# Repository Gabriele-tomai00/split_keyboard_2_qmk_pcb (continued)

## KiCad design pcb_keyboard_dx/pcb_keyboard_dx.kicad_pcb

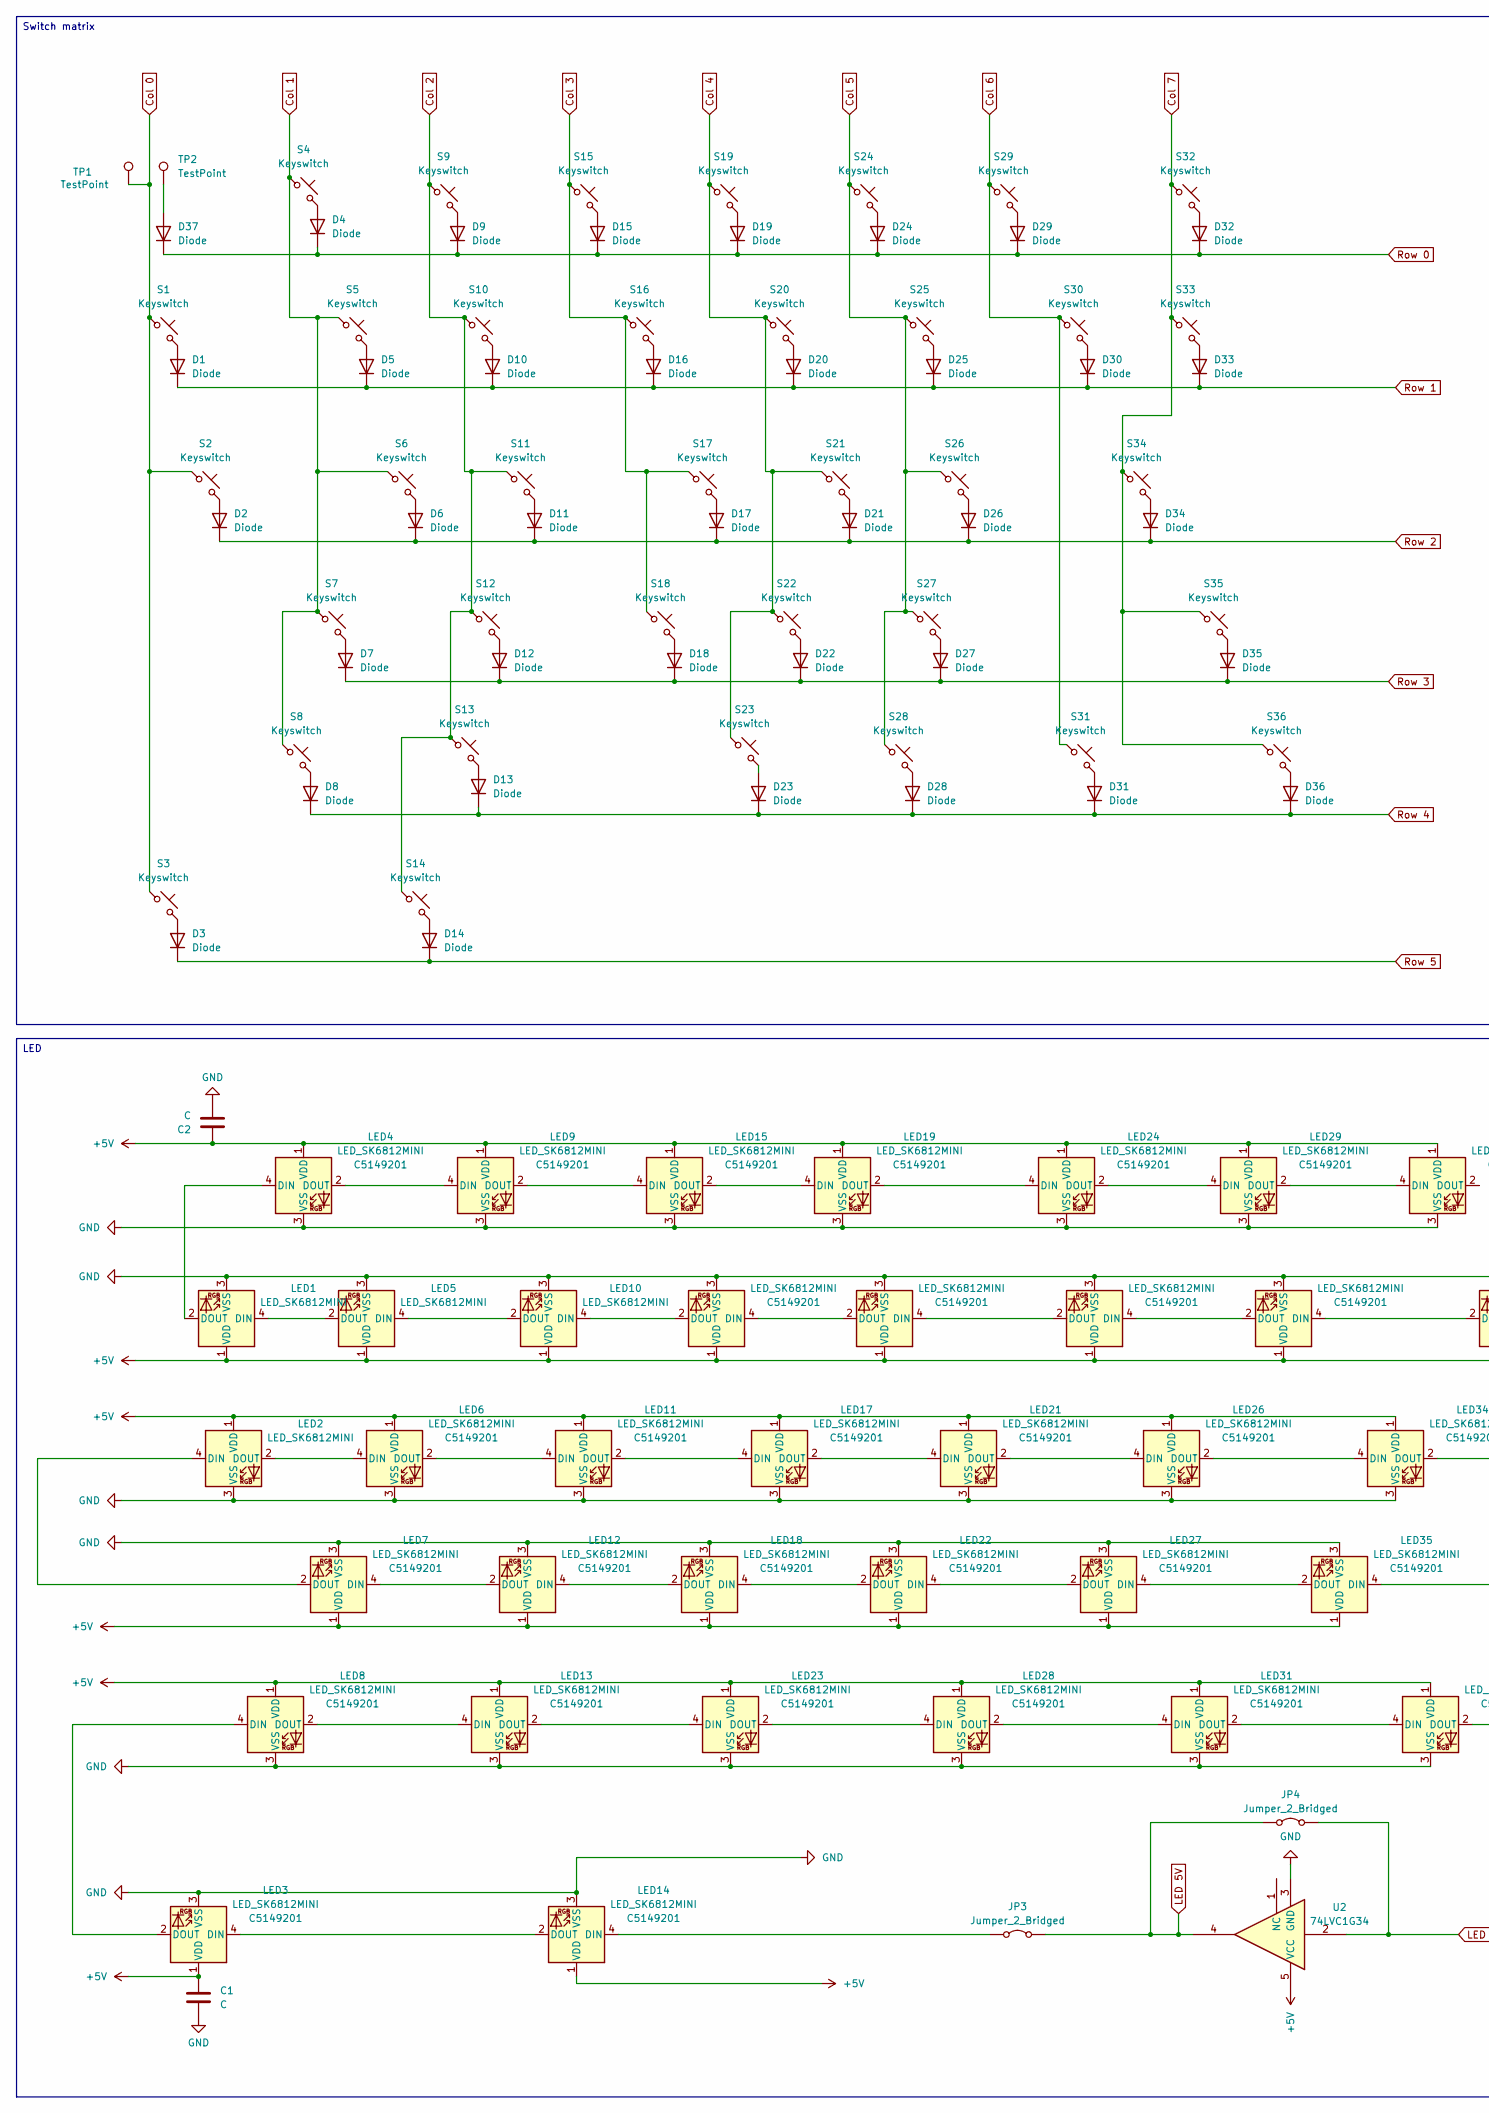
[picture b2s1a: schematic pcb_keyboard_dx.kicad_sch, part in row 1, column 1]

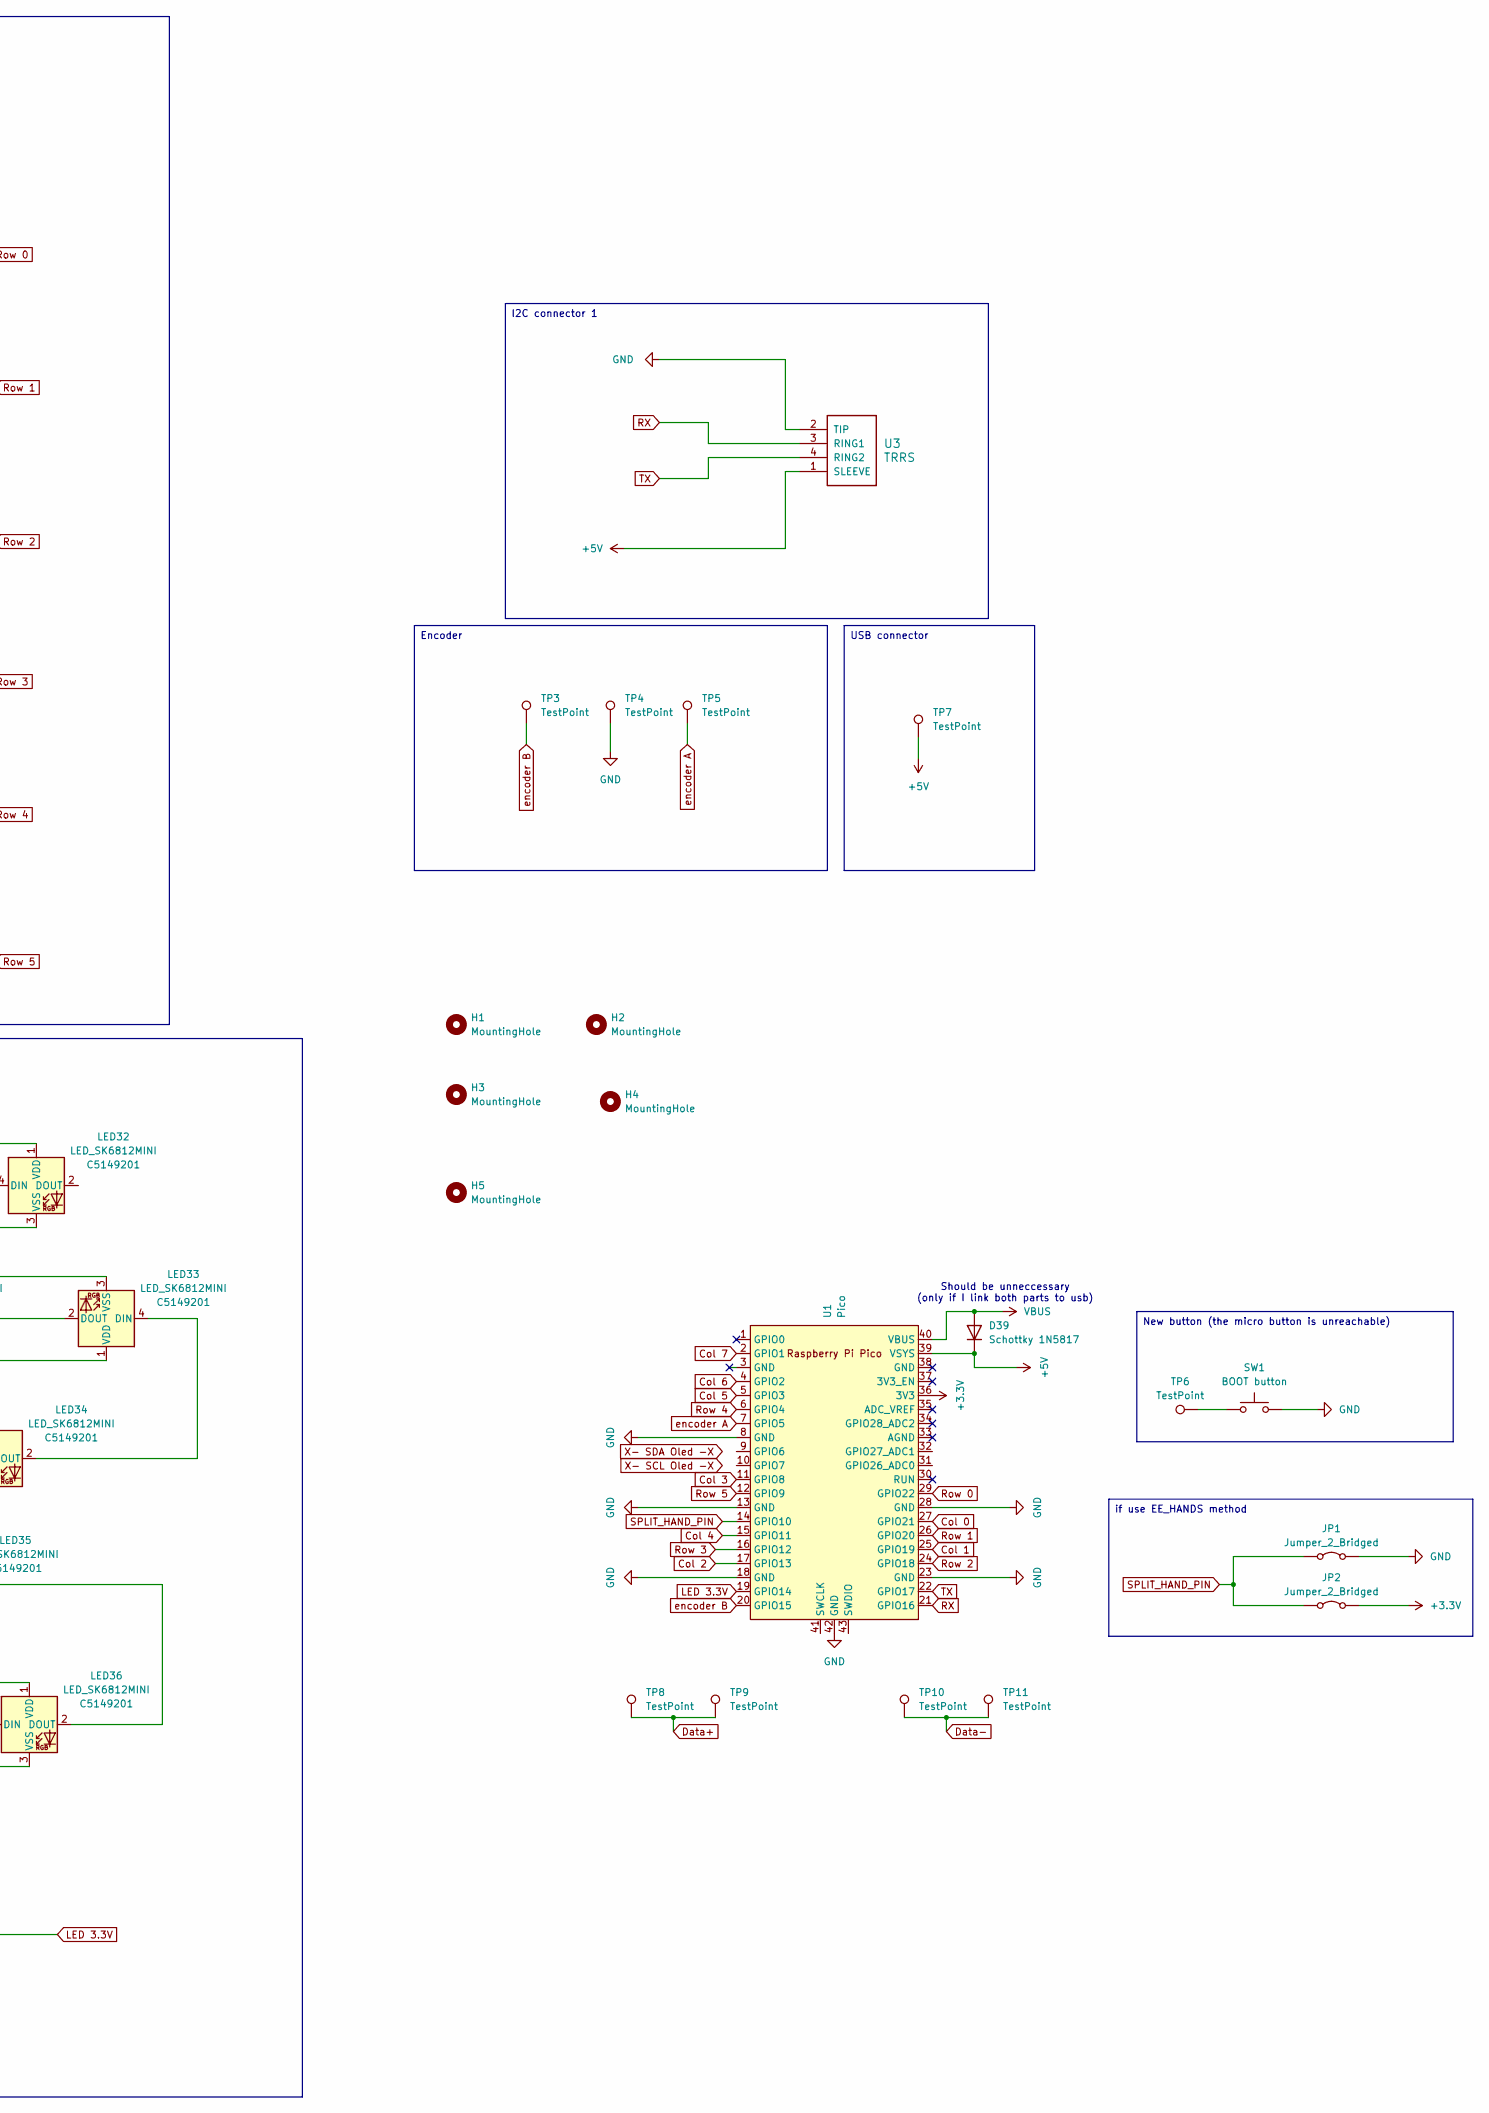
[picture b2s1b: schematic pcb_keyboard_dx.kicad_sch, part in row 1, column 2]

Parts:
C1, C2: C; C_1812_4532Metric_Pad1.57x3.40mm_HandSolder
D1, D2, D3, D4, D5, D6, D7, D8, D9, D10, D11, D12, D13, D14, D15, D16, D17, D18, D19, D20, D21, D22, D23, D24, D25, D26, D27, D28, D29, D30, D31, D32, D33, D34, D35, D36, D37: Diode; D_SOD-123_DO-35_Hybrid_DoubleSided_V2
D39: Schottky 1N5817; D_SOD-123_DO-35_Hybrid_DoubleSided_V2
H1, H2, H3, H4: MountingHole; MountingHole_2.2mm_M2
H5: MountingHole; MountingHole_3.2mm_M3
JP1, JP2, JP3, JP4: Jumper_2_Bridged; SolderJumper-2_P1.3mm_Bridged2Bar_Pad1.0x1.5mm
LED1, LED2, LED3, LED4, LED5, LED6, LED7, LED8, LED9, LED10, LED11, LED12, LED13, LED14, LED15, LED16, LED17, LED18, LED19, LED20, LED21, LED22, LED23, LED24, LED25, LED26, LED27, LED28, LED29, LED30, LED31, LED32, LED33, LED34, LED35, LED36: LED_SK6812MINI; LCSC C5149201
S1, S2, S4, S5, S6, S7, S9, S10, S11, S12, S15, S16, S17, S18, S19, S20, S21, S22, S24, S25, S26, S27, S29, S30: Keyswitch; Hotswap_MX_1.00u
S3: Keyswitch; Choc_V1_1.00u
S8: Keyswitch; Hotswap_MX_1.75u
S13, S33: Keyswitch; Hotswap_MX_1.50u
S14: Keyswitch; Choc_V1_1.75u
S23, S28, S31, S36: Keyswitch; Hotswap_MX_1.25u
S32: Keyswitch; Hotswap_MX_2.00u
S34: Keyswitch; Hotswap_MX_2.25u
S35: Keyswitch; Hotswap_MX_2.75u
SW1: BOOT button; Button_TL3342
TP1, TP2, TP3, TP4, TP5, TP6, TP7, TP8, TP9, TP10, TP11: TestPoint; PinHeader_1x01_P2.54mm_Vertical
U1: Pico; RPi_Pico_SMD_TH
U2: 74LVC1G34; SOT-353_SC-70-5_Handsoldering
U3: TRRS; TRRS_PJ-320A

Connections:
+3.3V: JP2.2 (B), U1.36 (3V3)
+5V: C1.1, C2.1, D39.1 (K), LED1.1 (VDD), LED2.1 (VDD), LED3.1 (VDD), LED4.1 (VDD), LED5.1 (VDD), LED6.1 (VDD), LED7.1 (VDD), LED8.1 (VDD), LED9.1 (VDD), LED10.1 (VDD), LED11.1 (VDD), LED12.1 (VDD), LED13.1 (VDD), LED14.1 (VDD), LED15.1 (VDD), LED16.1 (VDD), LED17.1 (VDD), LED18.1 (VDD), LED19.1 (VDD), LED20.1 (VDD), LED21.1 (VDD), LED22.1 (VDD), LED23.1 (VDD), LED24.1 (VDD), LED25.1 (VDD), LED26.1 (VDD), LED27.1 (VDD), LED28.1 (VDD), LED29.1 (VDD), LED30.1 (VDD), LED31.1 (VDD), LED32.1 (VDD), LED33.1 (VDD), LED34.1 (VDD), LED35.1 (VDD), LED36.1 (VDD), TP7.1, U1.39 (VSYS), U2.5 (VCC), U3.1 (SLEEVE)
Col 0: S1.1, S2.1, S3.1, TP1.1, U1.27 (GPIO21)
Col 1: S4.1, S5.1, S6.1, S7.1, S8.1, U1.25 (GPIO19)
Col 2: S9.1, S10.1, S11.1, S12.1, S13.1, S14.1, U1.17 (GPIO13)
Col 3: S15.1, S16.1, S17.1, S18.1, U1.11 (GPIO8)
Col 4: S19.1, S20.1, S21.1, S22.1, S23.1, U1.15 (GPIO11)
Col 5: S24.1, S25.1, S26.1, S27.1, S28.1, U1.5 (GPIO3)
Col 6: S29.1, S30.1, S31.1, U1.4 (GPIO2)
Col 7: S32.1, S33.1, S34.1, S35.1, S36.1, U1.2 (GPIO1)
Data+: TP8.1, TP9.1
Data-: TP10.1, TP11.1
GND: C1.2, C2.2, JP1.2 (B), LED1.3 (VSS), LED2.3 (VSS), LED3.3 (VSS), LED4.3 (VSS), LED5.3 (VSS), LED6.3 (VSS), LED7.3 (VSS), LED8.3 (VSS), LED9.3 (VSS), LED10.3 (VSS), LED11.3 (VSS), LED12.3 (VSS), LED13.3 (VSS), LED14.3 (VSS), LED15.3 (VSS), LED16.3 (VSS), LED17.3 (VSS), LED18.3 (VSS), LED19.3 (VSS), LED20.3 (VSS), LED21.3 (VSS), LED22.3 (VSS), LED23.3 (VSS), LED24.3 (VSS), LED25.3 (VSS), LED26.3 (VSS), LED27.3 (VSS), LED28.3 (VSS), LED29.3 (VSS), LED30.3 (VSS), LED31.3 (VSS), LED32.3 (VSS), LED33.3 (VSS), LED34.3 (VSS), LED35.3 (VSS), LED36.3 (VSS), SW1.2, TP4.1, U1.8 (GND), U1.13 (GND), U1.18 (GND), U1.23 (GND), U1.28 (GND), U1.42 (GND), U2.3 (GND), U3.2 (TIP)
LED 3.3V: JP4.2 (B), U1.19 (GPIO14), U2.2
LED 5V: JP3.2 (B), JP4.1 (A), U2.4
unnamed: D1.2 (A), S1.2
unnamed: D2.2 (A), S2.2
unnamed: D3.2 (A), S3.2
unnamed: D4.2 (A), S4.2
unnamed: D5.2 (A), S5.2
unnamed: D6.2 (A), S6.2
unnamed: D7.2 (A), S7.2
unnamed: D8.2 (A), S8.2
unnamed: D9.2 (A), S9.2
unnamed: D10.2 (A), S10.2
unnamed: D11.2 (A), S11.2
unnamed: D12.2 (A), S12.2
unnamed: D13.2 (A), S13.2
unnamed: D14.2 (A), S14.2
unnamed: D15.2 (A), S15.2
unnamed: D16.2 (A), S16.2
unnamed: D17.2 (A), S17.2
unnamed: D18.2 (A), S18.2
unnamed: D19.2 (A), S19.2
unnamed: D20.2 (A), S20.2
unnamed: D21.2 (A), S21.2
unnamed: D22.2 (A), S22.2
unnamed: D23.2 (A), S23.2
unnamed: D24.2 (A), S24.2
unnamed: D25.2 (A), S25.2
unnamed: D26.2 (A), S26.2
unnamed: D27.2 (A), S27.2
unnamed: D28.2 (A), S28.2
unnamed: D29.2 (A), S29.2
unnamed: D30.2 (A), S30.2
unnamed: D31.2 (A), S31.2
unnamed: D32.2 (A), S32.2
unnamed: D33.2 (A), S33.2
unnamed: D34.2 (A), S34.2
unnamed: D35.2 (A), S35.2
unnamed: D36.2 (A), S36.2
unnamed: D37.2 (A), TP2.1
unnamed: JP3.1 (A), LED14.4 (DIN)
unnamed: LED1.4 (DIN), LED5.2 (DOUT)
unnamed: LED1.2 (DOUT), LED4.4 (DIN)
unnamed: LED2.4 (DIN), LED7.2 (DOUT)
unnamed: LED2.2 (DOUT), LED6.4 (DIN)
unnamed: LED3.2 (DOUT), LED8.4 (DIN)
unnamed: LED4.2 (DOUT), LED9.4 (DIN)
unnamed: LED10.4 (DIN), LED16.2 (DOUT)
unnamed: LED5.4 (DIN), LED10.2 (DOUT)
unnamed: LED6.2 (DOUT), LED11.4 (DIN)
unnamed: LED11.2 (DOUT), LED17.4 (DIN)
unnamed: LED12.4 (DIN), LED18.2 (DOUT)
unnamed: LED7.4 (DIN), LED12.2 (DOUT)
unnamed: LED8.2 (DOUT), LED13.4 (DIN)
unnamed: LED13.2 (DOUT), LED23.4 (DIN)
unnamed: LED3.4 (DIN), LED14.2 (DOUT)
unnamed: LED9.2 (DOUT), LED15.4 (DIN)
unnamed: LED15.2 (DOUT), LED19.4 (DIN)
unnamed: LED16.4 (DIN), LED20.2 (DOUT)
unnamed: LED17.2 (DOUT), LED21.4 (DIN)
unnamed: LED18.4 (DIN), LED22.2 (DOUT)
unnamed: LED19.2 (DOUT), LED24.4 (DIN)
unnamed: LED20.4 (DIN), LED25.2 (DOUT)
unnamed: LED21.2 (DOUT), LED26.4 (DIN)
unnamed: LED22.4 (DIN), LED27.2 (DOUT)
unnamed: LED23.2 (DOUT), LED28.4 (DIN)
unnamed: LED24.2 (DOUT), LED29.4 (DIN)
unnamed: LED25.4 (DIN), LED30.2 (DOUT)
unnamed: LED26.2 (DOUT), LED34.4 (DIN)
unnamed: LED27.4 (DIN), LED35.2 (DOUT)
unnamed: LED28.2 (DOUT), LED31.4 (DIN)
unnamed: LED29.2 (DOUT), LED32.4 (DIN)
unnamed: LED30.4 (DIN), LED33.2 (DOUT)
unnamed: LED31.2 (DOUT), LED36.4 (DIN)
unnamed: LED33.4 (DIN), LED34.2 (DOUT)
unnamed: LED35.4 (DIN), LED36.2 (DOUT)
unnamed: SW1.1, TP6.1
RX: U1.21 (GPIO16), U3.3 (RING1)
Row 0: D4.1 (K), D9.1 (K), D15.1 (K), D19.1 (K), D24.1 (K), D29.1 (K), D32.1 (K), D37.1 (K), U1.29 (GPIO22)
Row 1: D1.1 (K), D5.1 (K), D10.1 (K), D16.1 (K), D20.1 (K), D25.1 (K), D30.1 (K), D33.1 (K), U1.26 (GPIO20)
Row 2: D2.1 (K), D6.1 (K), D11.1 (K), D17.1 (K), D21.1 (K), D26.1 (K), D34.1 (K), U1.24 (GPIO18)
Row 3: D7.1 (K), D12.1 (K), D18.1 (K), D22.1 (K), D27.1 (K), D35.1 (K), U1.16 (GPIO12)
Row 4: D8.1 (K), D13.1 (K), D23.1 (K), D28.1 (K), D31.1 (K), D36.1 (K), U1.6 (GPIO4)
Row 5: D3.1 (K), D14.1 (K), U1.12 (GPIO9)
SPLIT_HAND_PIN: JP1.1 (A), JP2.1 (A), U1.14 (GPIO10)
TX: U1.22 (GPIO17), U3.4 (RING2)
VBUS: D39.2 (A), U1.40 (VBUS)
encoder A: TP5.1, U1.7 (GPIO5)
encoder B: TP3.1, U1.20 (GPIO15)

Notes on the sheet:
LED
New button (the micro button is unreachable)
USB connector
Switch matrix
if use EE_HANDS method
Encoder
I2C connector 1
Should be unneccessary (only if I link both parts to usb)

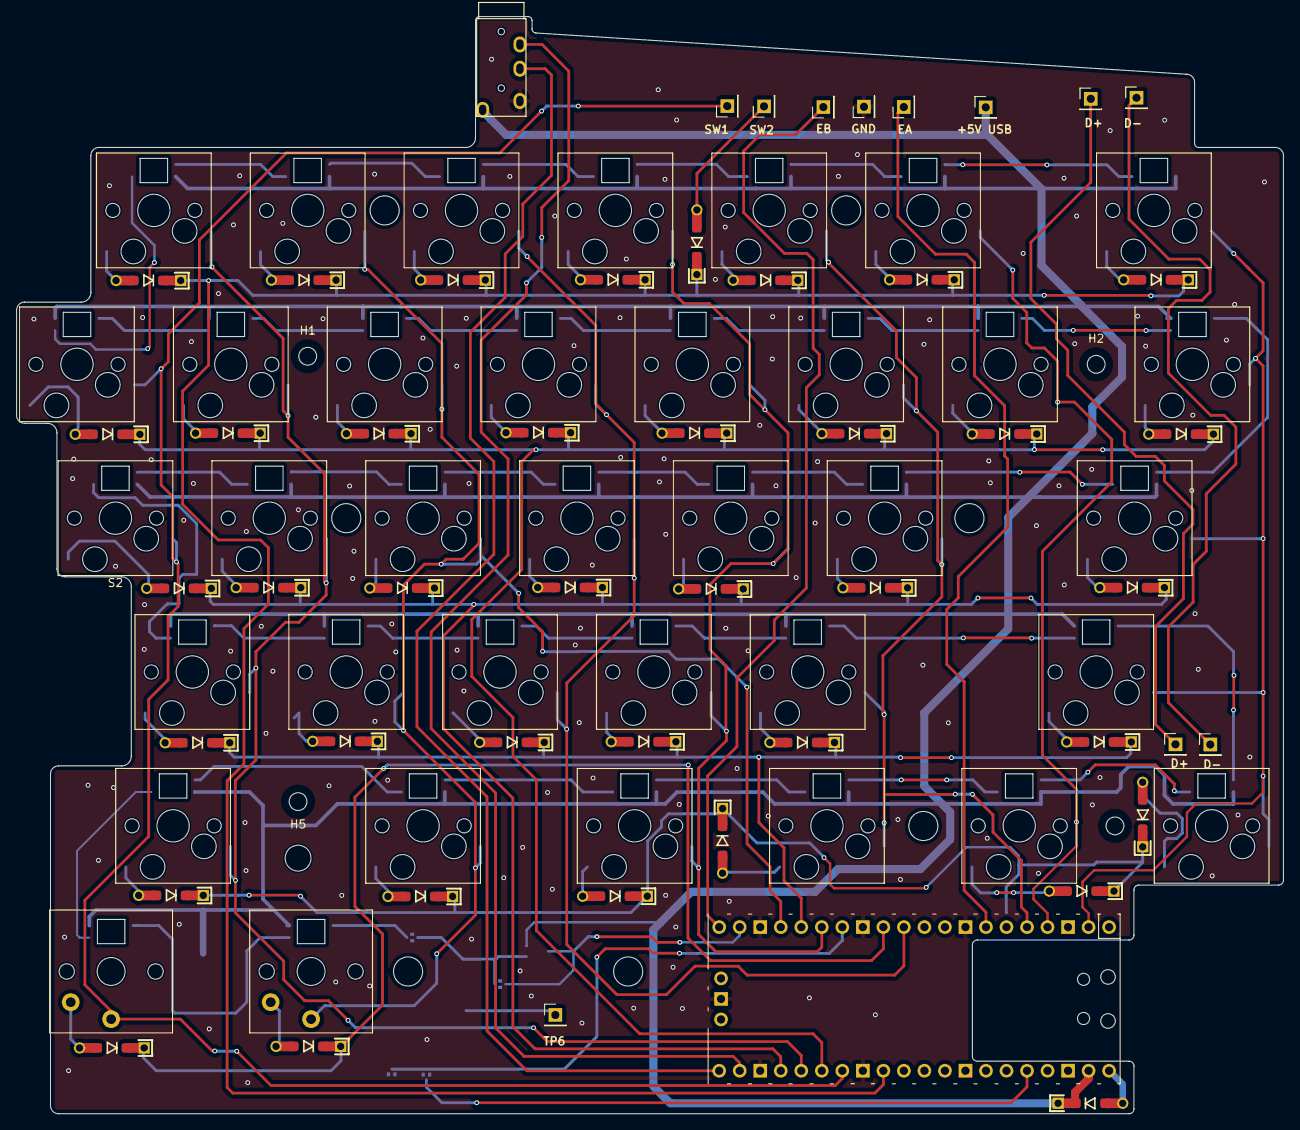
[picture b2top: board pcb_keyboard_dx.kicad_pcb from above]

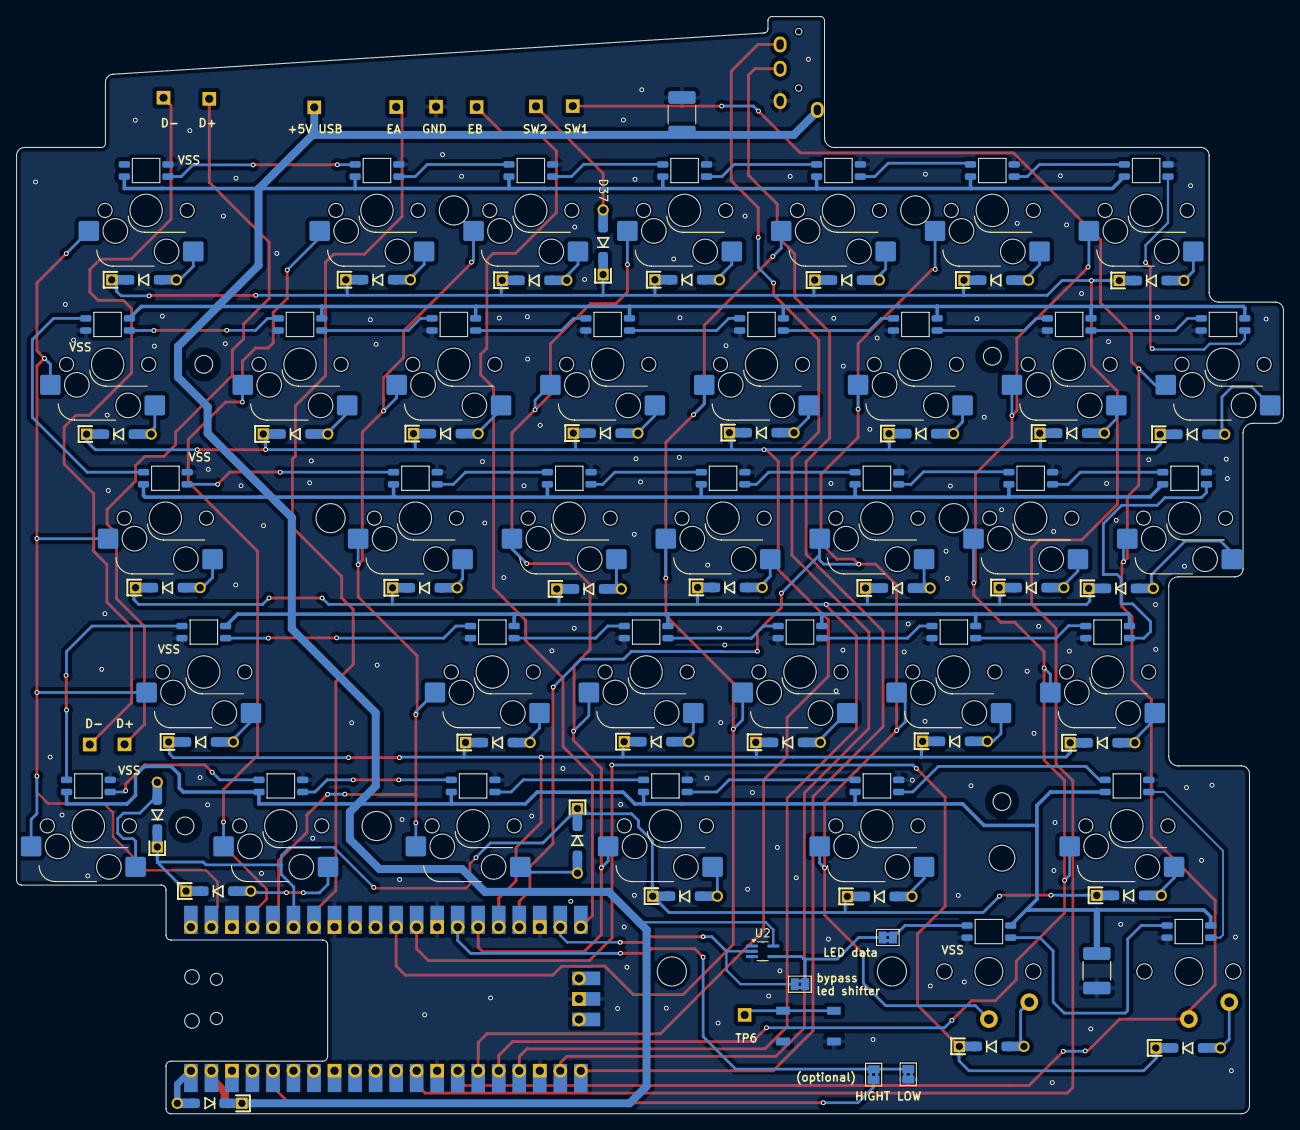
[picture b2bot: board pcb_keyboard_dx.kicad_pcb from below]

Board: 2 copper layers, 156.8 x 135.8 mm, 136 parts (82 on the bottom side), 101 nets.

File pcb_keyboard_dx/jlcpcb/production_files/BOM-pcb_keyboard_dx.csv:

Comment,Designator,Footprint,LCSC,Quantity
BOOT button,SW1,Button_TL3342,C115351,1
LED_SK6812MINI,"LED1,LED10,LED11,LED12,LED13,LED14,LED15,LED16,LED17,LED18,LED19,LED2,LED20,LED21,LED22,LED23,LED24,LED25,LED26,LED27,LED28,LED29,LED3,LED30,LED31,LED32,LED33,LED34,LED35,LED36,LED4,LED5,LED6,LED7,LED8,LED9",LED_SK6812MINI,C5149201,36
Keyswitch,S3,Choc_V1_1.00u,,1
Keyswitch,S8,Hotswap_MX_1.75u,,1
Keyswitch,S18,Hotswap_MX_1.00u,,1
Pico,U1,RPi_Pico_SMD_TH,,1
Keyswitch,S6,Hotswap_MX_1.00u,,1
Keyswitch,S32,Hotswap_MX_2.00u,,1
TRRS,U3,TRRS_PJ-320A,,1
Keyswitch,S33,Hotswap_MX_1.50u,,1
Keyswitch,S25,Hotswap_MX_1.00u,,1
Keyswitch,S5,Hotswap_MX_1.00u,,1
Keyswitch,S7,Hotswap_MX_1.00u,,1
Keyswitch,S36,Hotswap_MX_1.25u,,1
Keyswitch,S30,Hotswap_MX_1.00u,,1
Keyswitch,S2,Hotswap_MX_1.00u,,1
Keyswitch,S27,Hotswap_MX_1.00u,,1
Keyswitch,S9,Hotswap_MX_1.00u,,1
Keyswitch,S10,Hotswap_MX_1.00u,,1
Keyswitch,S1,Hotswap_MX_1.00u,,1
Keyswitch,S13,Hotswap_MX_1.50u,,1
Keyswitch,S17,Hotswap_MX_1.00u,,1
TestPoint,TP6,PinHeader_1x01_P2.54mm_Vertical,,1
Keyswitch,S23,Hotswap_MX_1.25u,,1
TestPoint,TP4,PinHeader_1x01_P2.54mm_Vertical,,1
Keyswitch,S21,Hotswap_MX_1.00u,,1
Keyswitch,S31,Hotswap_MX_1.25u,,1
Keyswitch,S28,Hotswap_MX_1.25u,,1
Keyswitch,S24,Hotswap_MX_1.00u,,1
Keyswitch,S35,Hotswap_MX_2.75u,,1
Keyswitch,S26,Hotswap_MX_1.00u,,1
TestPoint,TP5,PinHeader_1x01_P2.54mm_Vertical,,1
Keyswitch,S11,Hotswap_MX_1.00u,,1
TestPoint,TP2,PinHeader_1x01_P2.54mm_Vertical,,1
Keyswitch,S4,Hotswap_MX_1.00u,,1
TestPoint,TP3,PinHeader_1x01_P2.54mm_Vertical,,1
Keyswitch,S12,Hotswap_MX_1.00u,,1
Keyswitch,S14,Choc_V1_1.75u,,1
Keyswitch,S20,Hotswap_MX_1.00u,,1
Keyswitch,S19,Hotswap_MX_1.00u,,1
TestPoint,TP1,PinHeader_1x01_P2.54mm_Vertical,,1
Keyswitch,S22,Hotswap_MX_1.00u,,1
Keyswitch,S15,Hotswap_MX_1.00u,,1
Keyswitch,S16,Hotswap_MX_1.00u,,1
Keyswitch,S29,Hotswap_MX_1.00u,,1
Keyswitch,S34,Hotswap_MX_2.25u,,1
Jumper_2_Bridged,JP2,SolderJumper-2_P1.3mm_Bridged2Bar_Pad1.0x1.5mm,,1
Diode,D11,D_SOD-123_DO-35_Hybrid_DoubleSided_V2,,1
Diode,D9,D_SOD-123_DO-35_Hybrid_DoubleSided_V2,,1
Diode,D24,D_SOD-123_DO-35_Hybrid_DoubleSided_V2,,1
Diode,D12,D_SOD-123_DO-35_Hybrid_DoubleSided_V2,,1
Diode,D25,D_SOD-123_DO-35_Hybrid_DoubleSided_V2,,1
Diode,D3,D_SOD-123_DO-35_Hybrid_DoubleSided_V2,,1
Diode,D22,D_SOD-123_DO-35_Hybrid_DoubleSided_V2,,1
Diode,D33,D_SOD-123_DO-35_Hybrid_DoubleSided_V2,,1
Diode,D7,D_SOD-123_DO-35_Hybrid_DoubleSided_V2,,1
Diode,D30,D_SOD-123_DO-35_Hybrid_DoubleSided_V2,,1
Diode,D14,D_SOD-123_DO-35_Hybrid_DoubleSided_V2,,1
Diode,D15,D_SOD-123_DO-35_Hybrid_DoubleSided_V2,,1
Diode,D16,D_SOD-123_DO-35_Hybrid_DoubleSided_V2,,1
Diode,D1,D_SOD-123_DO-35_Hybrid_DoubleSided_V2,,1
Diode,D6,D_SOD-123_DO-35_Hybrid_DoubleSided_V2,,1
Diode,D17,D_SOD-123_DO-35_Hybrid_DoubleSided_V2,,1
Diode,D37,D_SOD-123_DO-35_Hybrid_DoubleSided_V2,,1
Diode,D28,D_SOD-123_DO-35_Hybrid_DoubleSided_V2,,1
Diode,D36,D_SOD-123_DO-35_Hybrid_DoubleSided_V2,,1
Diode,D18,D_SOD-123_DO-35_Hybrid_DoubleSided_V2,,1
Diode,D34,D_SOD-123_DO-35_Hybrid_DoubleSided_V2,,1
Diode,D21,D_SOD-123_DO-35_Hybrid_DoubleSided_V2,,1
Diode,D19,D_SOD-123_DO-35_Hybrid_DoubleSided_V2,,1
Jumper_2_Bridged,JP1,SolderJumper-2_P1.3mm_Bridged2Bar_Pad1.0x1.5mm,,1
Diode,D35,D_SOD-123_DO-35_Hybrid_DoubleSided_V2,,1
Diode,D10,D_SOD-123_DO-35_Hybrid_DoubleSided_V2,,1
Diode,D31,D_SOD-123_DO-35_Hybrid_DoubleSided_V2,,1
Diode,D23,D_SOD-123_DO-35_Hybrid_DoubleSided_V2,,1
Diode,D29,D_SOD-123_DO-35_Hybrid_DoubleSided_V2,,1
Diode,D4,D_SOD-123_DO-35_Hybrid_DoubleSided_V2,,1
Diode,D20,D_SOD-123_DO-35_Hybrid_DoubleSided_V2,,1
Diode,D8,D_SOD-123_DO-35_Hybrid_DoubleSided_V2,,1
Diode,D27,D_SOD-123_DO-35_Hybrid_DoubleSided_V2,,1
Diode,D26,D_SOD-123_DO-35_Hybrid_DoubleSided_V2,,1
Diode,D2,D_SOD-123_DO-35_Hybrid_DoubleSided_V2,,1
Diode,D32,D_SOD-123_DO-35_Hybrid_DoubleSided_V2,,1
Diode,D5,D_SOD-123_DO-35_Hybrid_DoubleSided_V2,,1
Diode,D13,D_SOD-123_DO-35_Hybrid_DoubleSided_V2,,1
Diode,D38,D_SOD-123_DO-35_Hybrid_DoubleSided_V2,,1
Jumper_2_Bridged,JP3,SolderJumper-2_P1.3mm_Bridged2Bar_Pad1.0x1.5mm,,1

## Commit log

2025-06-10 upload files
2025-06-10 level shifter added also for sx part
2025-06-10 added d+ and d- bus
2025-06-25 stessi GPIO per dx e sx
2025-06-25 Rimuovi .DS_Store dal tracking
2025-06-25 gitignore aggiornato per kicad projects
2025-06-25 Rimuovi file ignorati dal tracking
2025-08-09 tastiera con rj11 mandata in stampa
2025-09-22 firmware added
2025-09-22 gitignore updated for qmk
2026-01-29 create new folder for kicad, updated 3d_models, update readme
2026-01-29 moved all img in /images
2026-01-29 added key matrix wiring chapter in readme
2026-01-29 change names of kicad files
2026-01-29 added 3d print info and repository structure info
2026-01-29 small fix to redame visualization
2026-01-29 added firmware and updated instructions
2026-02-08 vial_config.vil uploaded
2026-02-08 fix repo structure in readme
2026-02-08 added .dxf files in readme
2026-02-08 remove 'Report In Progress' alert
